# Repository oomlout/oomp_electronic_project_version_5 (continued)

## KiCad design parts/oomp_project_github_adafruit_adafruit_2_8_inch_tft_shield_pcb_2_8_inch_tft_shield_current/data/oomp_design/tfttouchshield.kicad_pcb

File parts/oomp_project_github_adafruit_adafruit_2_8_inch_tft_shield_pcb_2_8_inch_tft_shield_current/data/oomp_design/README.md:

# OOMP KiCad design copy

Open `tfttouchshield.kicad_pro` (or the `.kicad_pcb` / `.kicad_sch`) in KiCad. Local OOMP libraries are under `libraries/`. Original inputs are preserved in [../original/](../original/).

Only verified unchanged installed KiCad defaults were renamed. Modified, custom, unmatched and unavailable items remain unchanged. Soldering variants are never swapped during conversion. Existing pad coordinates, nets and UUIDs are preserved.

See [conversion_report.yaml](conversion_report.yaml) for every conversion and skip. Copy this directory before editing; regeneration refuses to overwrite edited design files.

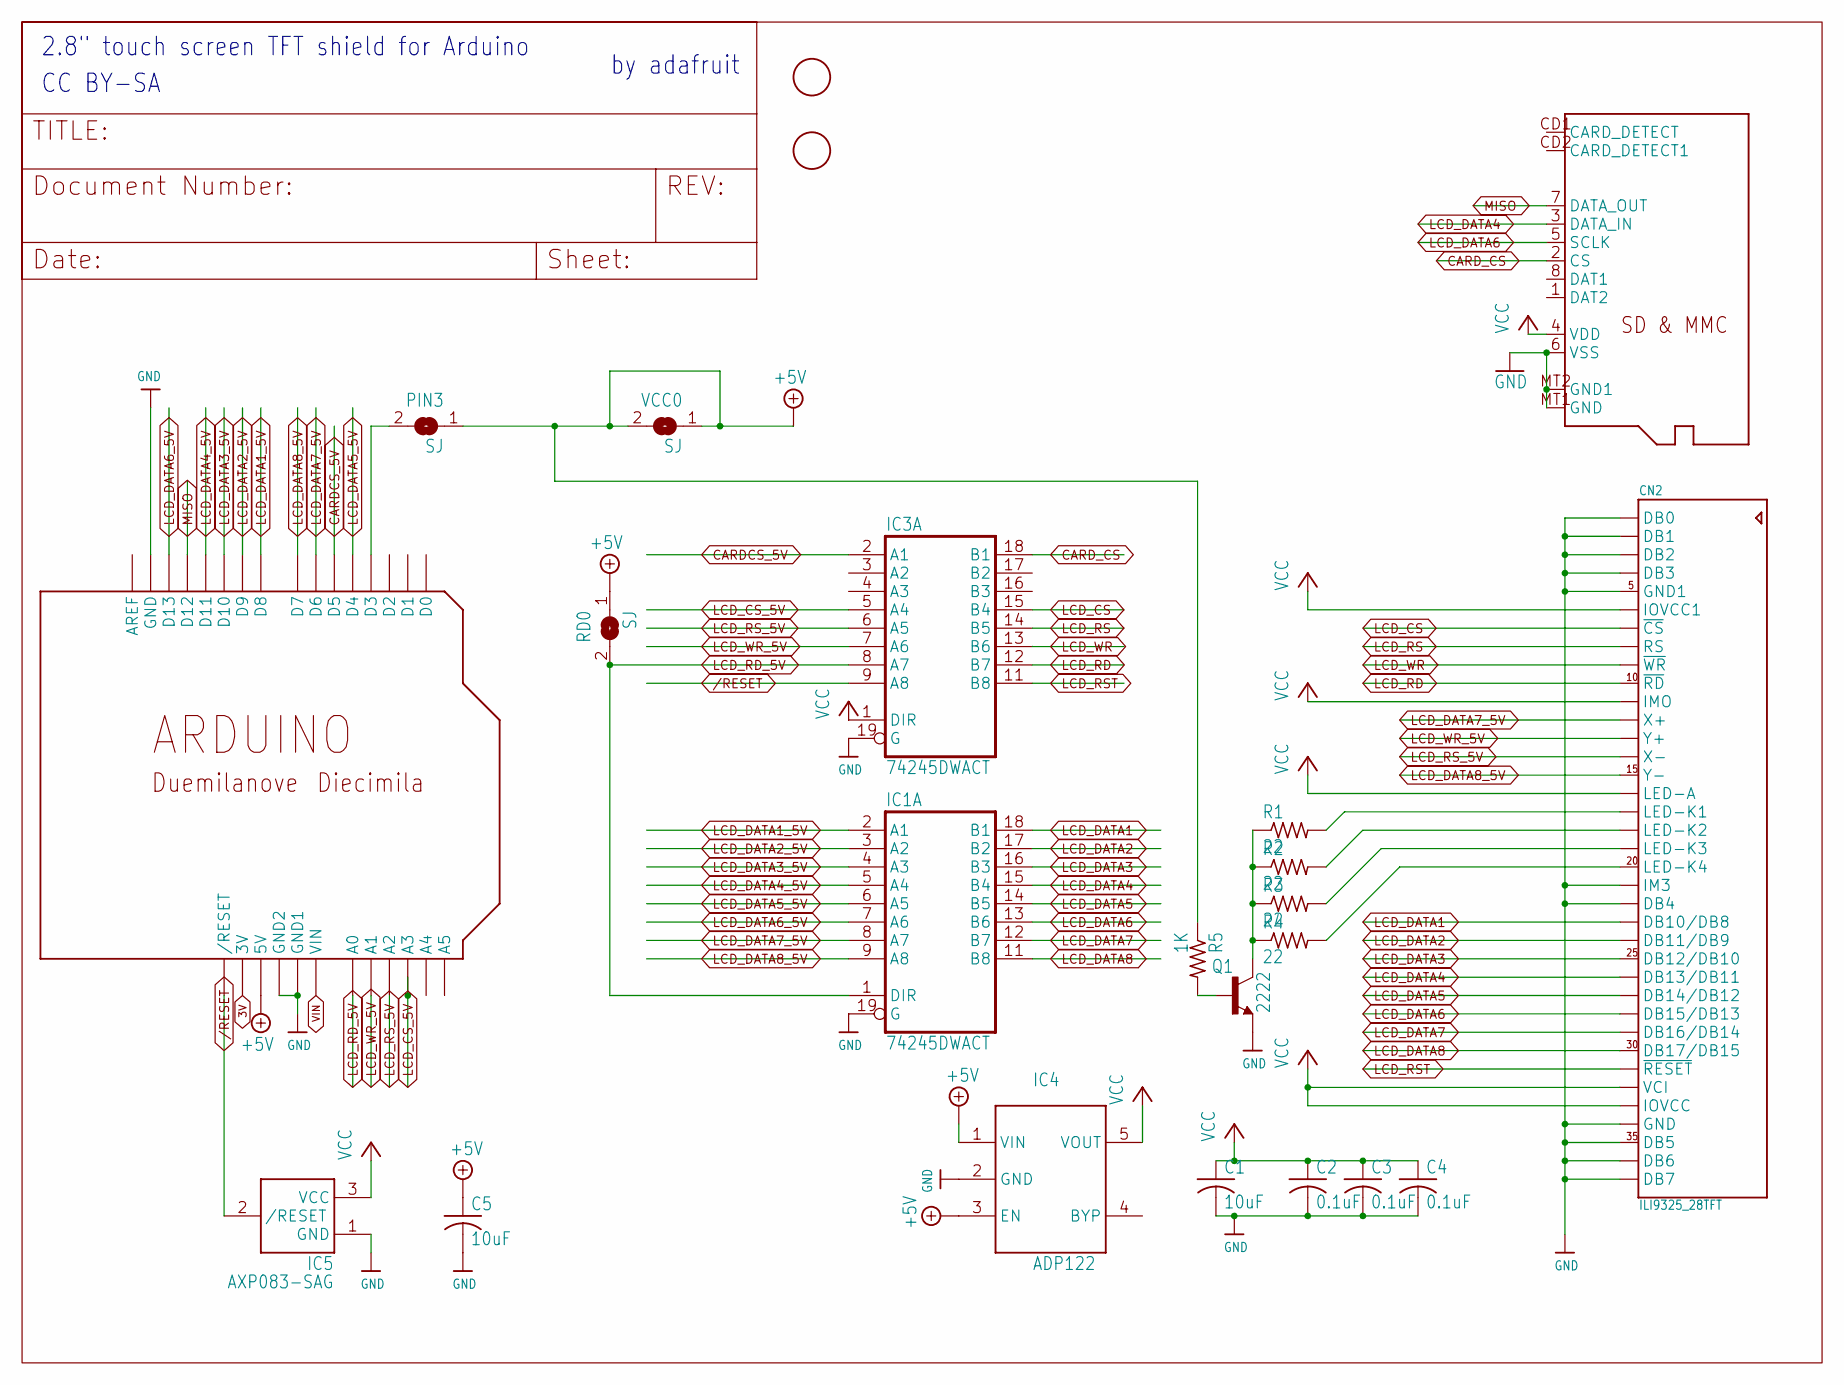
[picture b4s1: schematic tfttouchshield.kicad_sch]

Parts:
C1, C5: 10uF; C0805K
C2, C3, C4: 0.1uF; C0805K
CN2: ILI9325_28TFT; ILI9325_28INCH_TS
IC1, IC3: 74245DWACT; SO20W
IC4: ADP122; SOT23-5L
IC5: AXP083-SAG; SOT23
PIN3: SJ
Q1: 2222; SOT23-BEC
R1, R2, R3, R4: 22; R0805
R5: 1K; R0805
RD0: SJ
U$2: ARDUINO-NOHOLE
U$3: MICROSD
U$10, U$11: FIDUCIAL; FIDUCIAL_1MM
VCC0: SJ

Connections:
3V: U$2.3V
+5V: C5.1, IC4.1 (VIN), IC4.3 (EN), PIN3.1, R5.1, RD0.1, U$2.5V, VCC0.1, VCC0.2
/RESET: IC3.9 (A8), IC5.2 (/RESET), U$2.RESET (/RESET)
CARDCS_5V: IC3.2 (A1), U$2.D5
CARD_CS: IC3.18 (B1), U$3.2 (CS)
GND: C1.2, C2.2, C3.2, C4.2, C5.2, CN2.1 (DB0), CN2.2 (DB1), CN2.3 (DB2), CN2.4 (DB3), CN2.5 (GND1), CN2.21 (IM3), CN2.22 (DB4), CN2.34 (GND), CN2.35 (DB5), CN2.36 (DB6), CN2.37 (DB7), IC1.10 (GND), IC1.19 (G), IC3.10 (GND), IC3.19 (G), IC4.2 (GND), IC5.1 (GND), Q1.E, U$2.GND, U$2.GND1, U$2.GND2, U$3.6 (VSS), U$3.MT1 (GND), U$3.MT2 (GND1)
LCD_CS: CN2.7 (~CS), IC3.15 (B4)
LCD_CS_5V: IC3.5 (A4), U$2.A3
LCD_DATA1: CN2.23 (DB10/DB8), IC1.18 (B1)
LCD_DATA1_5V: IC1.2 (A1), U$2.D8
LCD_DATA2: CN2.24 (DB11/DB9), IC1.17 (B2)
LCD_DATA2_5V: IC1.3 (A2), U$2.D9
LCD_DATA3: CN2.25 (DB12/DB10), IC1.16 (B3)
LCD_DATA3_5V: IC1.4 (A3), U$2.D10
LCD_DATA4: CN2.26 (DB13/DB11), IC1.15 (B4), U$3.3 (DATA_IN)
LCD_DATA4_5V: IC1.5 (A4), U$2.D11
LCD_DATA5: CN2.27 (DB14/DB12), IC1.14 (B5)
LCD_DATA5_5V: IC1.6 (A5), U$2.D4
LCD_DATA6: CN2.28 (DB15/DB13), IC1.13 (B6), U$3.5 (SCLK)
LCD_DATA6_5V: IC1.7 (A6), U$2.D13
LCD_DATA7: CN2.29 (DB16/DB14), IC1.12 (B7)
LCD_DATA7_5V: CN2.12 (X+), IC1.8 (A7), U$2.D6
LCD_DATA8: CN2.30 (DB17/DB15), IC1.11 (B8)
LCD_DATA8_5V: CN2.15 (Y-), IC1.9 (A8), U$2.D7
LCD_RD: CN2.10 (~RD), IC3.12 (B7)
LCD_RD_5V: IC1.1 (DIR), IC3.8 (A7), RD0.2, U$2.A0
LCD_RS: CN2.8 (RS), IC3.14 (B5)
LCD_RST: CN2.31 (~RESET), IC3.11 (B8)
LCD_RS_5V: CN2.14 (X-), IC3.6 (A5), U$2.A2
LCD_WR: CN2.9 (~WR), IC3.13 (B6)
LCD_WR_5V: CN2.13 (Y+), IC3.7 (A6), U$2.A1
MISO: U$2.D12, U$3.7 (DATA_OUT)
unnamed: CN2.20 (LED-K4), R4.2
unnamed: CN2.17 (LED-K1), R1.2
unnamed: CN2.18 (LED-K2), R2.2
unnamed: CN2.19 (LED-K3), R3.2
unnamed: Q1.C, R1.1, R2.1, R3.1, R4.1
unnamed: PIN3.2, U$2.D3
unnamed: Q1.B, R5.2
VCC: C1.1, C2.1, C3.1, C4.1, CN2.6 (IOVCC1), CN2.11 (IMO), CN2.16 (LED-A), CN2.32 (VCI), CN2.33 (IOVCC), IC1.20 (VCC), IC3.1 (DIR), IC3.20 (VCC), IC4.5 (VOUT), IC5.3 (VCC), U$3.4 (VDD)
VIN: U$2.VIN

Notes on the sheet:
CC BY-SA
2.8" touch screen TFT shield for Arduino
by adafruit~{}

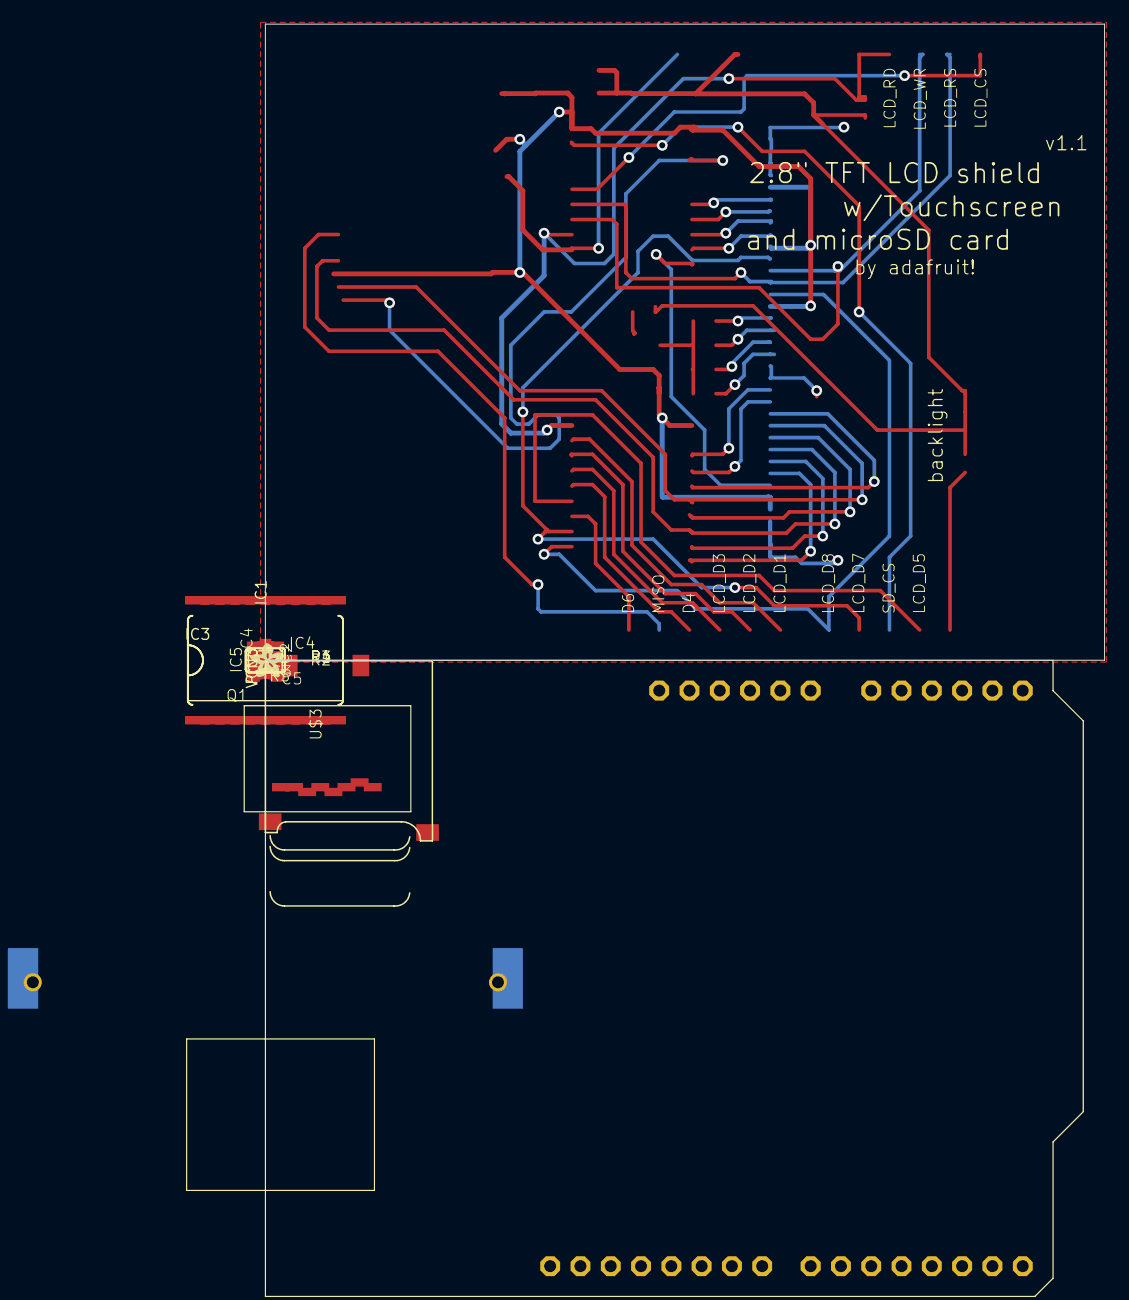
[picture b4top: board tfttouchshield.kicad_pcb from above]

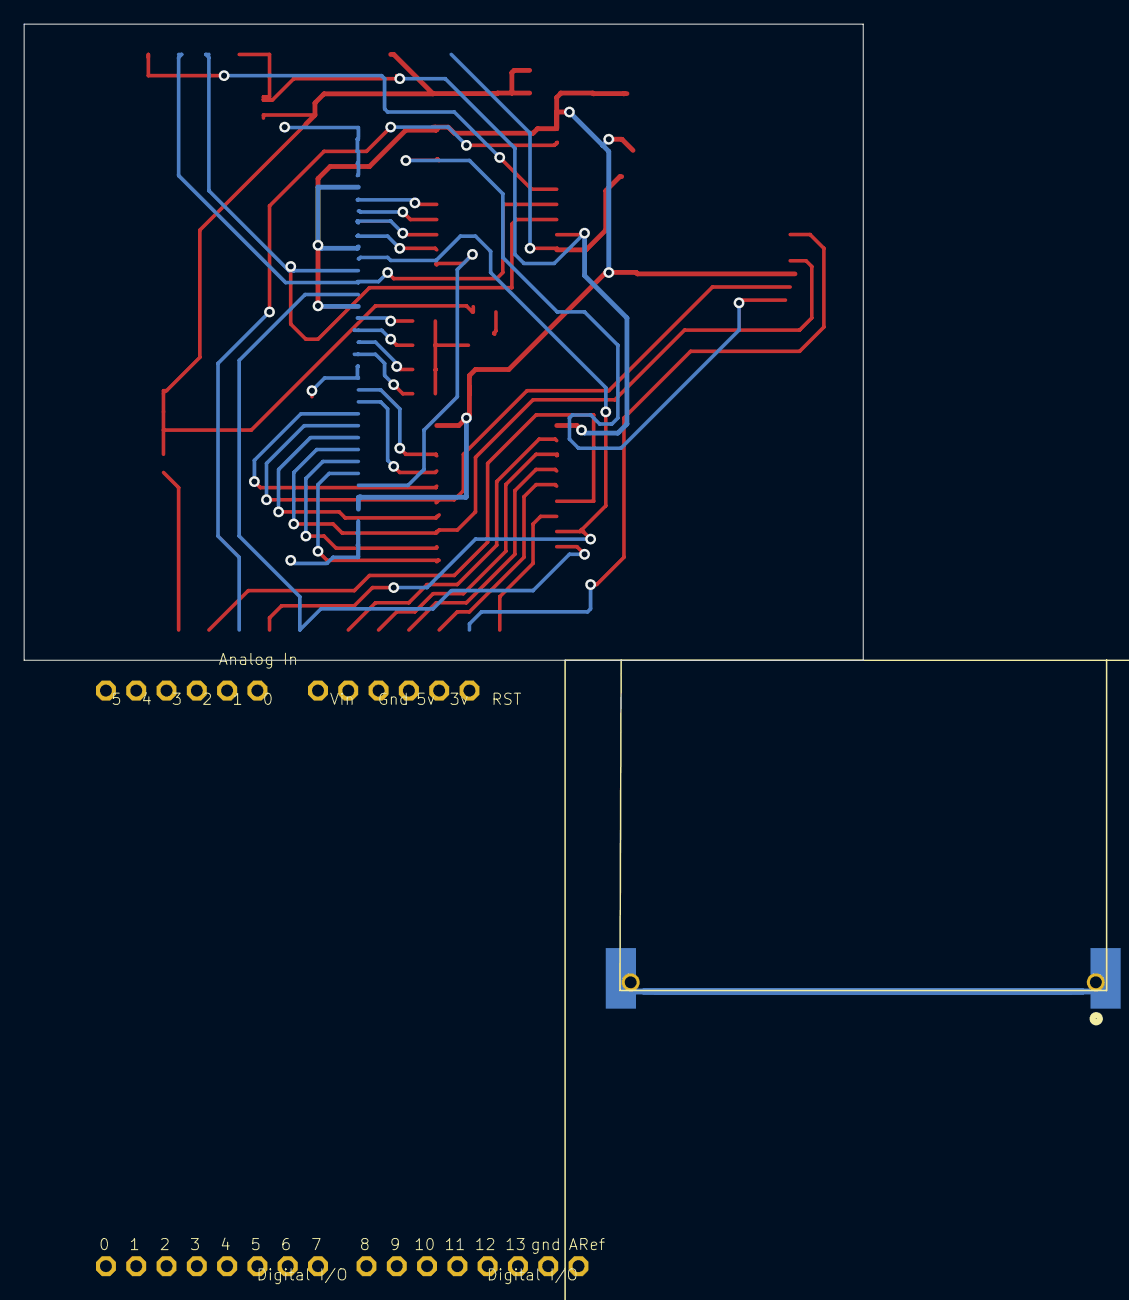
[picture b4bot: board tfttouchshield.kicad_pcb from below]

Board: 16 copper layers, 70.4 x 53.3 mm, 25 parts (2 on the bottom side), 39 nets.

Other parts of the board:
U$7: ADAFRUIT200MIL
U$9: OSHWLOGO_TOL_0.2

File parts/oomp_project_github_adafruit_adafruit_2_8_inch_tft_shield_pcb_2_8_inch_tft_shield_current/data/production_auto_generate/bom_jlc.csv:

Comment,Designator,Footprint,LCSC Part #
,U$7,tfttouchshield-import-fps:ADAFRUIT200MIL,
,U$9,tfttouchshield-import-fps:OSHWLOGO_TOL_0.2,
,"PIN3,RD0,VCC0",tfttouchshield-import-fps:SJ,
,IC5,tfttouchshield-import-fps:SOT23,
0.1uF,"C2,C3,C4",tfttouchshield-import-fps:C0805K,
10uF,"C1,C5",tfttouchshield-import-fps:C0805K,
1K,R5,tfttouchshield-import-fps:R0805,C17513
22,"R1,R2,R3,R4",tfttouchshield-import-fps:R0805,C2907310
2222,Q1,tfttouchshield-import-fps:SOT23-BEC,
74ACT245DW,"IC1,IC3",tfttouchshield-import-fps:SO20W,
ADP122,IC4,tfttouchshield-import-fps:SOT23-5L,
ARDUINO-NOHOLE,U$2,tfttouchshield-import-fps:ARDUINO-NOHOLE,
FIDUCIAL,"U$10,U$11",tfttouchshield-import-fps:FIDUCIAL_1MM,
ILI9325_28TFT,CN2,tfttouchshield-import-fps:ILI9325_28INCH_TS,
MICROSD,U$3,tfttouchshield-import-fps:MICROSD,
